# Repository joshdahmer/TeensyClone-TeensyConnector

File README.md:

# TeensyClone-TeensyConnector

KiCad files for PCB to connect Teensy 3.2 clone (https://github.com/joshdahmer/teensy-3.2-clone.kicad) to existing boards with female headers for Teensy 3.2 microcontrollers.

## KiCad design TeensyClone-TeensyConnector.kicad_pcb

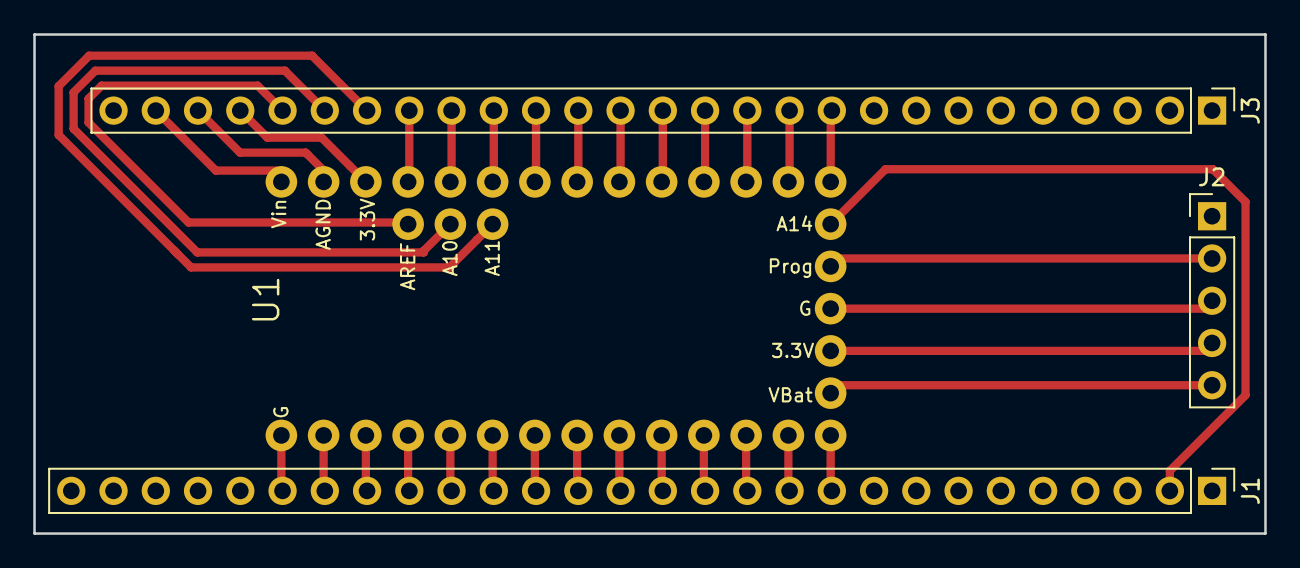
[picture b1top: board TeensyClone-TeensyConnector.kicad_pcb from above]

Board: 2 copper layers, 74.0 x 30.0 mm, 4 parts (0 on the bottom side), 34 nets.

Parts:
J1: CONN_01X28; Pin_Header_Straight_1x28_Pitch2.54mm
J2: CONN_01X05; Pin_Header_Straight_1x05_Pitch2.54mm
J3: CONN_01X27; Pin_Header_Straight_1x27_Pitch2.54mm
U1: Teensy_3.2; Teensy-3.2

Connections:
0: J1.22, U1.0
1: J1.21, U1.1
2: J1.20, U1.2
3: J1.19, U1.3
4: J1.18, U1.4
5: J1.17, U1.5
6: J1.16, U1.6
7: J1.15, U1.7
8: J1.14, U1.8
9: J1.13, U1.9
10: J1.12, U1.10
11: J1.11, U1.11
12: J1.10, U1.12
13: J3.10, U1.13
+3V3: J2.4, J3.2, J3.8, J3.24, U1.24, U1.31
A0: J3.11, U1.14
A1: J3.12, U1.15
A2: J3.13, U1.16
A3: J3.14, U1.17
A4: J3.15, U1.18
A5: J3.16, U1.19
A6: J3.17, U1.20
A7: J3.18, U1.21
A8: J3.19, U1.22
A9: J3.20, U1.23
A10: J3.22, U1.34
A11: J3.21, U1.33
A14/DAC: J1.2, U1.28
AGND: J3.25, U1.25
AREF: J3.23, U1.35
GND: J1.1, J1.8, J1.23, J1.28, J2.3, J3.1, U1.27, U1.30
PROG: J2.2, U1.29
VBAT: J2.5, U1.32
VIN: J3.26, U1.26

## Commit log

2017-10-26 Edit README
2017-10-26 Set theme jekyll-theme-cayman
